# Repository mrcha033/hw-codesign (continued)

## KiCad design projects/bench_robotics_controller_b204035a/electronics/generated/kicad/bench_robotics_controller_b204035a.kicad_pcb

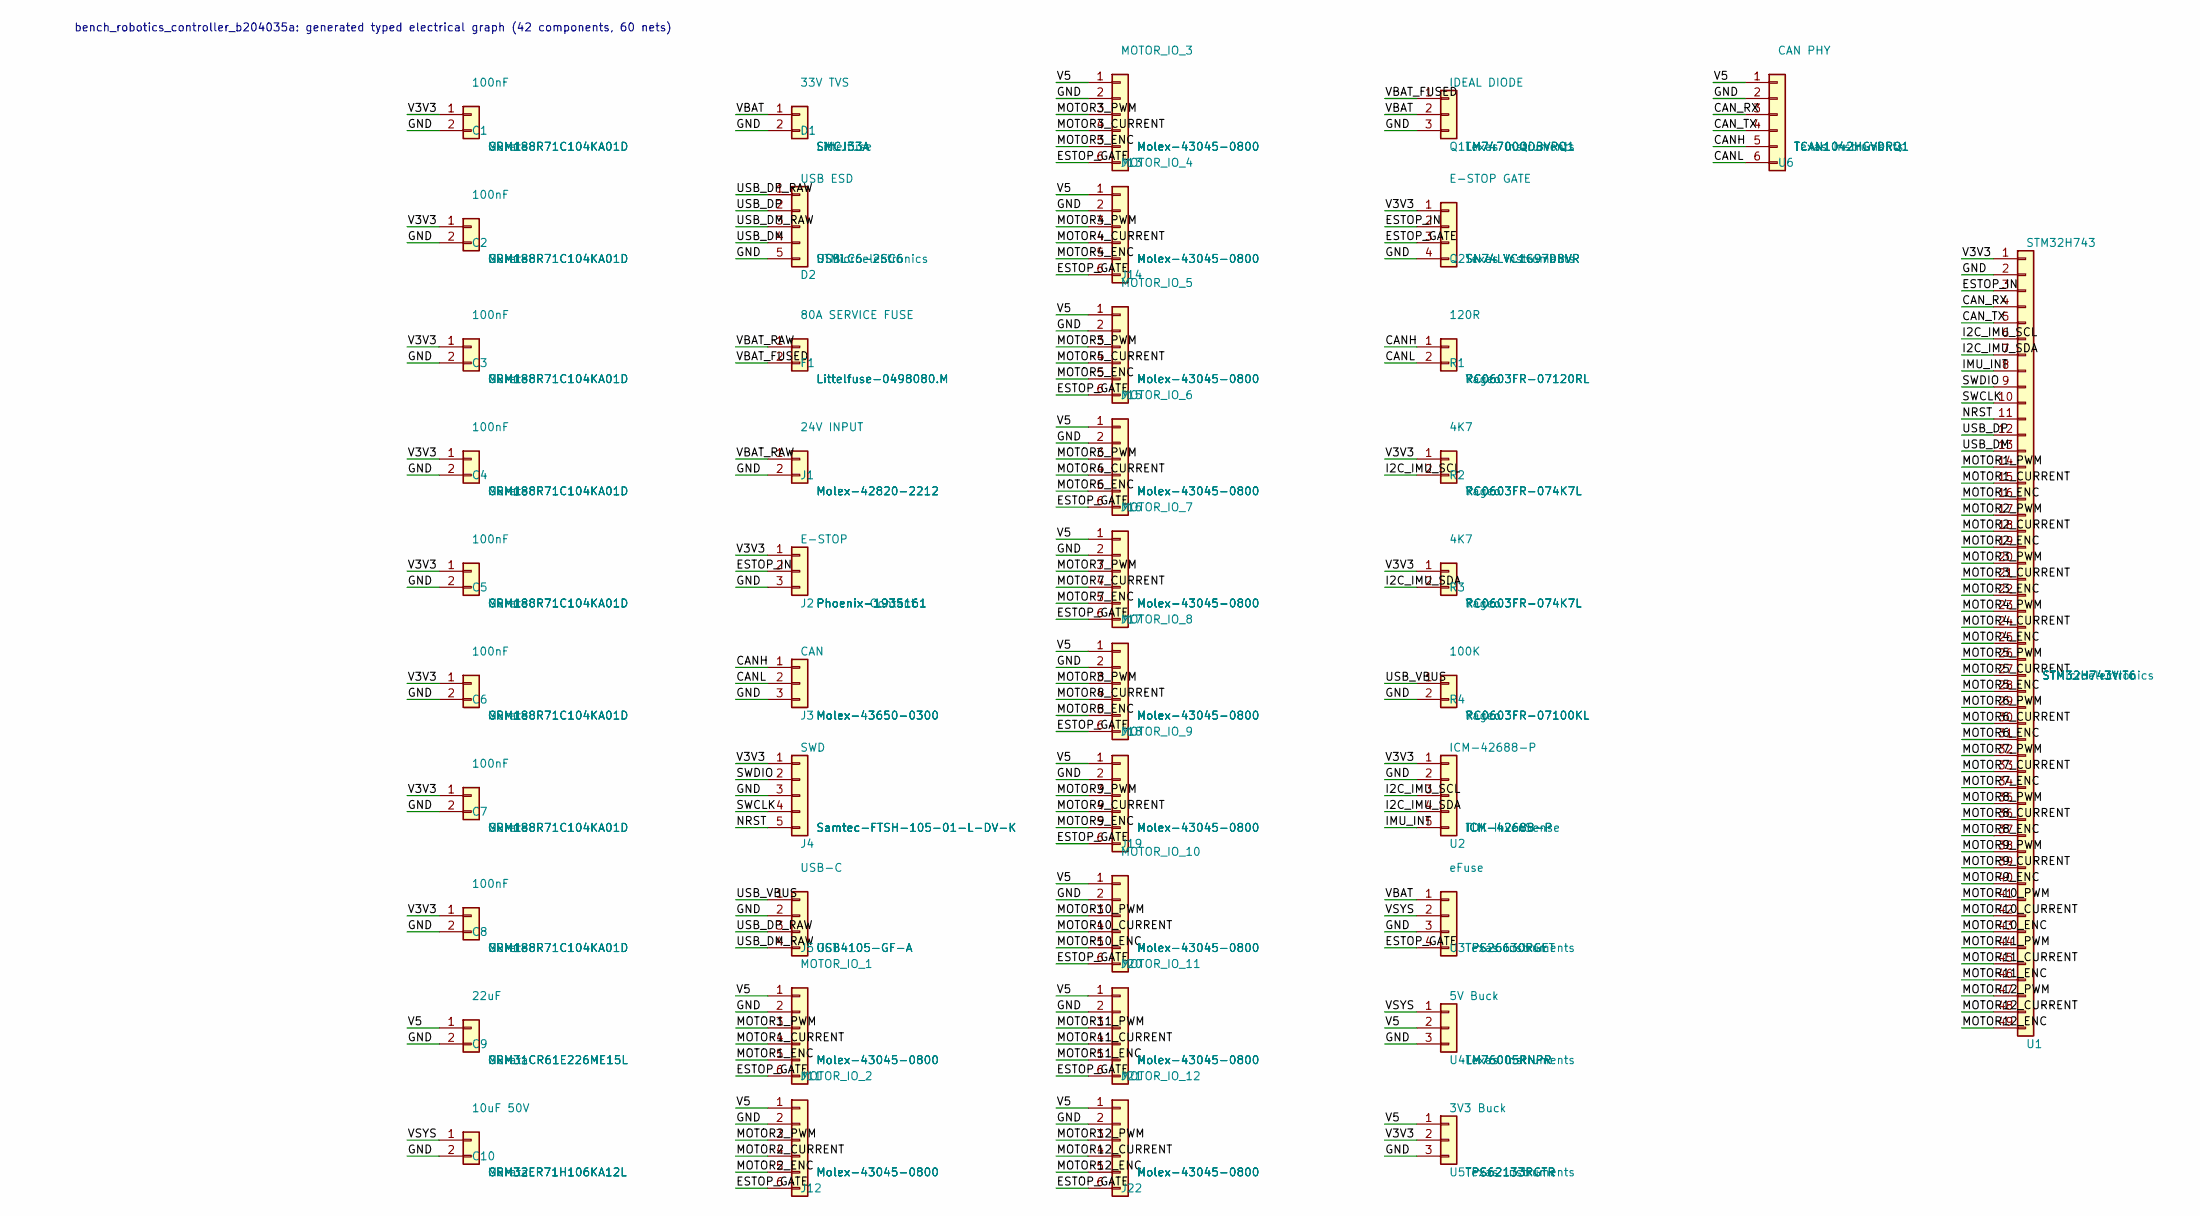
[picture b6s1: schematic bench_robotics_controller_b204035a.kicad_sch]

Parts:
C1, C2, C3, C4, C5, C6, C7, C8: 100nF; C_0603_1608Metric; MPN GRM188R71C104KA01D
C9: 22uF; C_1206_3216Metric; MPN GRM31CR61E226ME15L
C10: 10uF 50V; C_1210_3225Metric; MPN GRM32ER71H106KA12L
D1: 33V TVS; D_SMC; MPN SMCJ33A
D2: USB ESD; SOT-23-6; MPN USBLC6-2SC6
F1: 80A SERVICE FUSE; MIDI_Fuse; MPN Littelfuse-0498080.M
J1: 24V INPUT; MicroFit_2Pin; MPN Molex-42820-2212
J2: E-STOP; Phoenix_3Pin; MPN Phoenix-1935161
J3: CAN; MicroFit_3Pin; MPN Molex-43650-0300
J4: SWD; FTSH-105; MPN Samtec-FTSH-105-01-L-DV-K
J5: USB-C; USB_C_GCT_USB4105; MPN USB4105-GF-A
J11: MOTOR_IO_1; MicroFit_8Pin; MPN Molex-43045-0800
J12: MOTOR_IO_2; MicroFit_8Pin; MPN Molex-43045-0800
J13: MOTOR_IO_3; MicroFit_8Pin; MPN Molex-43045-0800
J14: MOTOR_IO_4; MicroFit_8Pin; MPN Molex-43045-0800
J15: MOTOR_IO_5; MicroFit_8Pin; MPN Molex-43045-0800
J16: MOTOR_IO_6; MicroFit_8Pin; MPN Molex-43045-0800
J17: MOTOR_IO_7; MicroFit_8Pin; MPN Molex-43045-0800
J18: MOTOR_IO_8; MicroFit_8Pin; MPN Molex-43045-0800
J19: MOTOR_IO_9; MicroFit_8Pin; MPN Molex-43045-0800
J20: MOTOR_IO_10; MicroFit_8Pin; MPN Molex-43045-0800
J21: MOTOR_IO_11; MicroFit_8Pin; MPN Molex-43045-0800
J22: MOTOR_IO_12; MicroFit_8Pin; MPN Molex-43045-0800
Q1: IDEAL DIODE; SOT-23-6; MPN LM74700QDBVRQ1
Q2: E-STOP GATE; SOT-23-6; MPN SN74LVC1G97DBVR
R1: 120R; R_0603_1608Metric; MPN RC0603FR-07120RL
R2, R3: 4K7; R_0603_1608Metric; MPN RC0603FR-074K7L
R4: 100K; R_0603_1608Metric; MPN RC0603FR-07100KL
U1: STM32H743; LQFP-100_14x14mm_P0.5mm; MPN STM32H743VIT6
U2: ICM-42688-P; LGA-14; MPN ICM-42688-P
U3: eFuse; VQFN-24-1EP; MPN TPS26630RGET
U4: 5V Buck; WQFN-30; MPN LM76005RNPR
U5: 3V3 Buck; VQFN-16; MPN TPS62133RGTR
U6: CAN PHY; SOIC-8_3.9x4.9mm_P1.27mm; MPN TCAN1042HGVDRQ1

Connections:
CANH: J3.1, R1.1, U6.5
CANL: J3.2, R1.2, U6.6
CAN_RX: U1.4, U6.3
CAN_TX: U1.5, U6.4
ESTOP_GATE: J11.6, J12.6, J13.6, J14.6, J15.6, J16.6, J17.6, J18.6, J19.6, J20.6, J21.6, J22.6, Q2.3, U3.4
ESTOP_IN: J2.2, Q2.2, U1.3
GND: C1.2, C2.2, C3.2, C4.2, C5.2, C6.2, C7.2, C8.2, C9.2, C10.2, D1.2, D2.5, J1.2, J2.3, J3.3, J4.3, J5.2, J11.2, J12.2, J13.2, J14.2, J15.2, J16.2, J17.2, J18.2, J19.2, J20.2, J21.2, J22.2, Q1.3, Q2.4, R4.2, U1.2, U2.2, U3.3, U4.3, U5.3, U6.2
I2C_IMU_SCL: R2.2, U1.6, U2.3
I2C_IMU_SDA: R3.2, U1.7, U2.4
IMU_INT: U1.8, U2.5
MOTOR1_CURRENT: J11.4, U1.15
MOTOR1_ENC: J11.5, U1.16
MOTOR1_PWM: J11.3, U1.14
MOTOR2_CURRENT: J12.4, U1.18
MOTOR2_ENC: J12.5, U1.19
MOTOR2_PWM: J12.3, U1.17
MOTOR3_CURRENT: J13.4, U1.21
MOTOR3_ENC: J13.5, U1.22
MOTOR3_PWM: J13.3, U1.20
MOTOR4_CURRENT: J14.4, U1.24
MOTOR4_ENC: J14.5, U1.25
MOTOR4_PWM: J14.3, U1.23
MOTOR5_CURRENT: J15.4, U1.27
MOTOR5_ENC: J15.5, U1.28
MOTOR5_PWM: J15.3, U1.26
MOTOR6_CURRENT: J16.4, U1.30
MOTOR6_ENC: J16.5, U1.31
MOTOR6_PWM: J16.3, U1.29
MOTOR7_CURRENT: J17.4, U1.33
MOTOR7_ENC: J17.5, U1.34
MOTOR7_PWM: J17.3, U1.32
MOTOR8_CURRENT: J18.4, U1.36
MOTOR8_ENC: J18.5, U1.37
MOTOR8_PWM: J18.3, U1.35
MOTOR9_CURRENT: J19.4, U1.39
MOTOR9_ENC: J19.5, U1.40
MOTOR9_PWM: J19.3, U1.38
MOTOR10_CURRENT: J20.4, U1.42
MOTOR10_ENC: J20.5, U1.43
MOTOR10_PWM: J20.3, U1.41
MOTOR11_CURRENT: J21.4, U1.45
MOTOR11_ENC: J21.5, U1.46
MOTOR11_PWM: J21.3, U1.44
MOTOR12_CURRENT: J22.4, U1.48
MOTOR12_ENC: J22.5, U1.49
MOTOR12_PWM: J22.3, U1.47
NRST: J4.5, U1.11
SWCLK: J4.4, U1.10
SWDIO: J4.2, U1.9
USB_DM: D2.4, U1.13
USB_DM_RAW: D2.3, J5.4
USB_DP: D2.2, U1.12
USB_DP_RAW: D2.1, J5.3
USB_VBUS: J5.1, R4.1
V3V3: C1.1, C2.1, C3.1, C4.1, C5.1, C6.1, C7.1, C8.1, J2.1, J4.1, Q2.1, R2.1, R3.1, U1.1, U2.1, U5.2
V5: C9.1, J11.1, J12.1, J13.1, J14.1, J15.1, J16.1, J17.1, J18.1, J19.1, J20.1, J21.1, J22.1, U4.2, U5.1, U6.1
VBAT: D1.1, Q1.2, U3.1
VBAT_FUSED: F1.2, Q1.1
VBAT_RAW: F1.1, J1.1
VSYS: C10.1, U3.2, U4.1

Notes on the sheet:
bench_robotics_controller_b204035a: generated typed electrical graph (42 components, 60 nets)

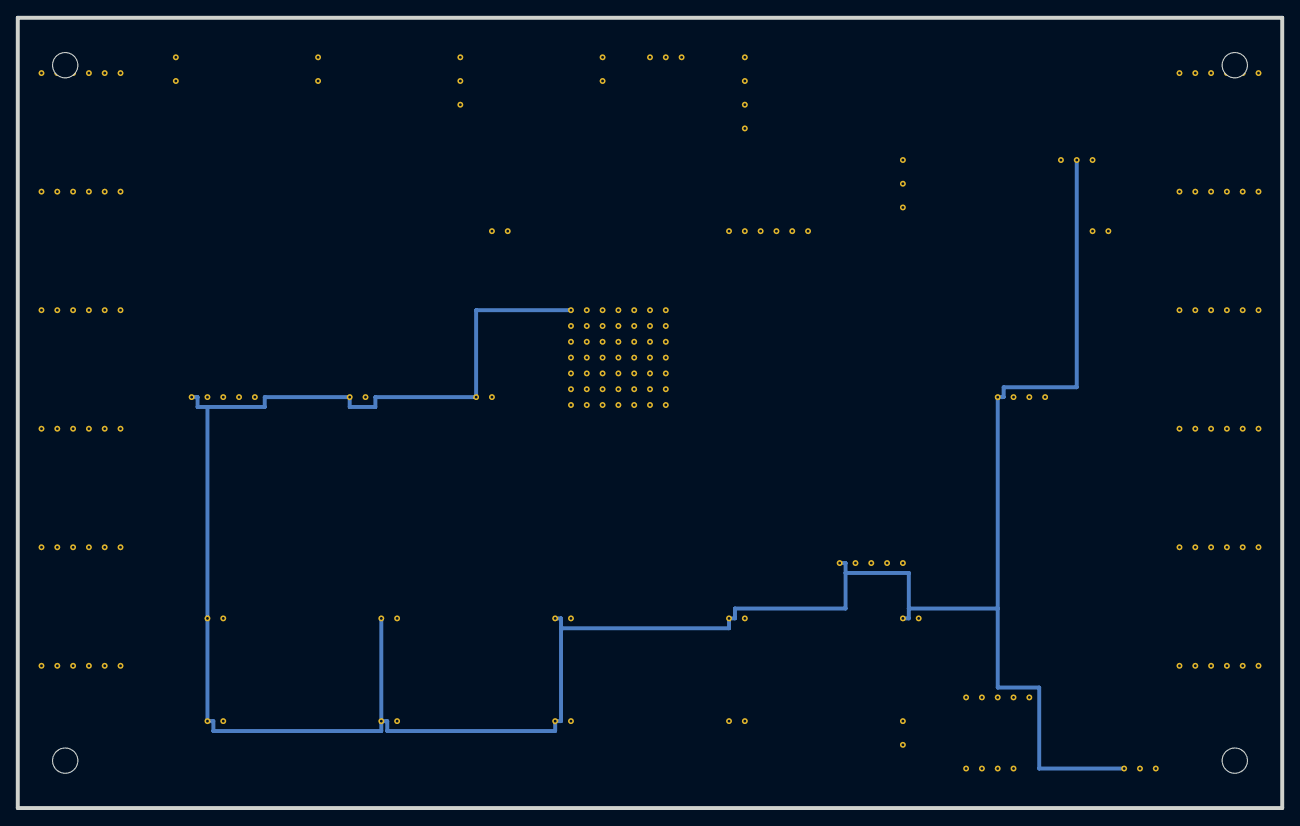
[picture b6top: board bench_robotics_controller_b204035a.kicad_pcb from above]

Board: 4 copper layers, 160.0 x 100.0 mm, 46 parts (0 on the bottom side), 60 nets.

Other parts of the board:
H1, H2, H3, H4: MountingHole; MountingHole_3.2mm_Pad

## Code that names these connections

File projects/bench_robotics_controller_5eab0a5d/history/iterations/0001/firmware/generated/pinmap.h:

#pragma once

#define PIN_ESTOP_IN "ESTOP_IN"
#define PIN_CAN_RX "CAN_RX"
#define PIN_CAN_TX "CAN_TX"
#define PIN_I2C_IMU_SCL "I2C_IMU_SCL"
#define PIN_I2C_IMU_SDA "I2C_IMU_SDA"
#define PIN_IMU_INT "IMU_INT"
#define PIN_USB_DP "USB_DP"
#define PIN_USB_DM "USB_DM"
#define PIN_MOTOR1_PWM "MOTOR1_PWM"
#define PIN_MOTOR1_CURRENT "MOTOR1_CURRENT"
#define PIN_MOTOR1_ENC "MOTOR1_ENC"
#define PIN_MOTOR2_PWM "MOTOR2_PWM"
#define PIN_MOTOR2_CURRENT "MOTOR2_CURRENT"
#define PIN_MOTOR2_ENC "MOTOR2_ENC"
#define PIN_MOTOR3_PWM "MOTOR3_PWM"
#define PIN_MOTOR3_CURRENT "MOTOR3_CURRENT"
#define PIN_MOTOR3_ENC "MOTOR3_ENC"
#define PIN_MOTOR4_PWM "MOTOR4_PWM"
#define PIN_MOTOR4_CURRENT "MOTOR4_CURRENT"
#define PIN_MOTOR4_ENC "MOTOR4_ENC"
#define PIN_MOTOR5_PWM "MOTOR5_PWM"
#define PIN_MOTOR5_CURRENT "MOTOR5_CURRENT"
#define PIN_MOTOR5_ENC "MOTOR5_ENC"
#define PIN_MOTOR6_PWM "MOTOR6_PWM"
#define PIN_MOTOR6_CURRENT "MOTOR6_CURRENT"
#define PIN_MOTOR6_ENC "MOTOR6_ENC"
#define PIN_MOTOR7_PWM "MOTOR7_PWM"
#define PIN_MOTOR7_CURRENT "MOTOR7_CURRENT"
#define PIN_MOTOR7_ENC "MOTOR7_ENC"
#define PIN_MOTOR8_PWM "MOTOR8_PWM"
#define PIN_MOTOR8_CURRENT "MOTOR8_CURRENT"
#define PIN_MOTOR8_ENC "MOTOR8_ENC"
#define PIN_MOTOR9_PWM "MOTOR9_PWM"
#define PIN_MOTOR9_CURRENT "MOTOR9_CURRENT"
#define PIN_MOTOR9_ENC "MOTOR9_ENC"
#define PIN_MOTOR10_PWM "MOTOR10_PWM"
#define PIN_MOTOR10_CURRENT "MOTOR10_CURRENT"
#define PIN_MOTOR10_ENC "MOTOR10_ENC"
#define PIN_MOTOR11_PWM "MOTOR11_PWM"
#define PIN_MOTOR11_CURRENT "MOTOR11_CURRENT"
#define PIN_MOTOR11_ENC "MOTOR11_ENC"
#define PIN_MOTOR12_PWM "MOTOR12_PWM"
#define PIN_MOTOR12_CURRENT "MOTOR12_CURRENT"
#define PIN_MOTOR12_ENC "MOTOR12_ENC"

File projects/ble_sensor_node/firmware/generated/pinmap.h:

#pragma once

#define PIN_I2C_SCL "P0.02"
#define PIN_I2C_SDA "P0.03"
#define PIN_CHG_STAT "P0.04"
#define PIN_TEMP_INT "P0.05"
#define PIN_FUEL_ALRT "P0.06"
#define PIN_LED_BLE "P0.08"
#define PIN_UART_TX "P0.28"
#define PIN_UART_RX "P0.29"
#define PIN_SWDCLK "SWDCLK"
#define PIN_SWO "SWO"
#define PIN_USB_DM "D-"
#define PIN_USB_DP "D+"

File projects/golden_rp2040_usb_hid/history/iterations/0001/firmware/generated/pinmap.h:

#pragma once

#define PIN_XIN "XIN"
#define PIN_XOUT "XOUT"
#define PIN_MCU_RUN "RUN"
#define PIN_USB_DM "USB_DM"
#define PIN_USB_DP "USB_DP"
#define PIN_QSPI_D3 "QSPI_SD3"
#define PIN_QSPI_CLK "QSPI_SCLK"
#define PIN_QSPI_MOSI "QSPI_SD0"
#define PIN_QSPI_D2 "QSPI_SD2"
#define PIN_QSPI_MISO "QSPI_SD1"
#define PIN_QSPI_CS "QSPI_CSn"

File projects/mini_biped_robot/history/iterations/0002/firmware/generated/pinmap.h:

#pragma once

#define PIN_XIN32 "PA00_XIN32"
#define PIN_XOUT32 "PA01_XOUT32"
#define PIN_IMU_INT1 "PA18_SERCOM3_2"
#define PIN_I2C_SDA "PA22_SDA"
#define PIN_I2C_SCL "PA23_SCL"
#define PIN_USB_DM "PA24_USBDM"
#define PIN_USB_DP "PA25_USBDP"
#define PIN_MCU_NRST "~RESETN"
#define PIN_VDDCORE "VDDCORE"

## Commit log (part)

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2026-06-14 Initial commit: hw-codesign-platform v0.1.0
    Hardware co-design platform CLI, MCP server, schemas, tests, and
    example quadruped robot controller project including electronics,
    firmware, mechanical, and iteration history.
2026-06-14 feat: component resolver, provenance tracking, and tscircuit backend gate
    - Add ComponentResolver and artifact_provenance to wire real component
    data (MPN, footprint, lifecycle) into the electrical graph
    - Introduce TSCircuitBackend as the first release-eligible compiled
    electronics backend; reference backend now explicitly blocks release
    - Move electronics design intent from .ato source files to annotated
    .intent.md files under electronics/intent/
2026-06-14 fix: update prepare_release logic to block on unresolved critical assumptions and adjust footprint parity checks
2026-06-15 feat: constraint-driven placement proposal layer (roadmap #5)
    Add structured, provenance-tagged component placement with a checkable
    constraint model, scoped as a placement proposal rather than autonomous
    layout.
    - placement.py: Placement/PlacementConstraint/PlacementProposal dataclasses;
    propose_placement derives board/mounting-hole keepouts, connector-edge
    (reusing max_connector_edge_distance_mm), decoupling-proximity (represented
2026-06-15 feat: add hw export-review command producing normalized review bundle (steps 2-3)
    service.export_review() aggregates persisted gate reports, placement
    proposal metadata, component resolution summary, requirements lowering
    summary, and assumption state into a single bundle.json. The canonical
    content (excluding generated_at) is SHA-256 hashed into bundle_hash so
    consecutive exports are byte-identical deterministically.
    cli.py wires the export-review subcommand and also stubs upload_review()
2026-06-15 test: add review bundle test suite (5 tests)
    Covers: schema validation of produced bundle, hash determinism across
    consecutive exports, HTML generation, graceful no-prior-checks path,
    and upload_review blocked-without-destination guard.
2026-06-15 feat: add hw_codesign.contracts public package with full tool registry and schemas
    Introduces `hw_codesign.contracts` as the single source of truth for the
    local-and-cloud MCP contract surface:
    - TOOL_REGISTRY: 36 ToolDef entries each carrying name, description,
    input_schema, output_schema, and execution_mode
    - 12 shared output schemas in _schemas.py (gate_report, gate_report_collection,
    electronics_source_result, repair_plan, iteration_result, etc.) referenced
2026-06-15 fix setup-uv action version
2026-06-15 fix: verify ESP32-S3 library, add Windows CI, strengthen atopile tests
    Component verification:
    - esp32s3_wroom_1: updated to verified: true, review_status: approved after
    checking against KiCad RF_Module library installed at
    /Applications/KiCad/KiCad.app/Contents/SharedSupport; corrected package
    from LCC-52 to LCC-41 (41 castellated pads + thermal), library_id from
    HW_Curated placeholder to RF_Module:ESP32-S3-WROOM-1, pin numbers and
2026-06-16 feat: sensor_data_logger second board family — 2-layer, ESP32-S3, USB-C
    Adds a complete second board template (sensor_data_logger) fully parallel
    to robotics_controller_full, with all generation paths dispatching on
    architecture:
    - electronics_design: build_sensor_data_logger_graph() for ESP32-S3-WROOM-1,
    USB-C/ESD/buck power tree, ICM-42688-P IMU, I2C pull-ups, UART debug header
    - board_layout: sensor_data_logger anchor table + _seed_table_for_graph() dispatch
2026-06-16 fix: Windows CI — bundle KiCAD symbols and fix tsx binary on win32
    74 tests were failing because kicad-symbols is only installed on the
    Linux CI runner (via apt). The Windows runner has no KiCAD, so
    kicad_sch_api throws LibraryError on every schematic generation call.
    Fix: bundle a minimal Connector_Generic.kicad_sym (Conn_01x01–50) in
    parts/kicad_symbols/ and add a session-scoped autouse fixture in
    conftest.py that sets KICAD_SYMBOL_DIR to the bundled path when no
2026-06-16 fix: use bundled KiCAD symbols on all platforms, pins inside unit sub-symbol
    Two issues remained after the previous fix:
    1. kicad_sch_api._extract_pins_from_symbol only finds pins inside the unit
    sub-symbol (e.g. Conn_01x02_1_1), but the generated file had pins at the
    parent symbol level. Locally list_pins() still worked via the embedded
    schematic copy, but on Windows CI the pin lookup path disagreed, causing
    "Missing generated schematic pin C1.1" for all 76 tests.
2026-06-16 fix: pass relative posix path to tscircuit CLI, expose stderr on failure
    The tscircuit CLI uses the entry file path to construct its dist output
    directory name. When given an absolute Windows path (D:\a\hw-cli\...),
    it creates dist/D:\a\hw-cli\... which contains a colon — invalid on
    Windows filesystems — causing a non-zero exit code.
    Fix: compute the entry path relative to platform_root (the cwd for the
    subprocess) and pass it as a POSIX-format string, e.g.
2026-06-16 fix: MCP protocol correctness — envelope gaps, python_netlist gate, stale detection
    - check_release_gate: accept python_netlist as release-eligible backend (was
    incorrectly blocked via backend_release_policy); use backend-specific required
    artifact list (compiled_netlist.json instead of gerbers/drill) and filter out
    intentionally-BLOCKED layout/manufacturing gates that python_netlist never emits
    - _enrich: replace setdefault with direct dict merge ({**result, **extra}) so
    safety-critical envelope fields (release_eligible, candidate_only,
2026-06-16 docs: fix envelope accuracy, add missing tools, badges, and visual polish
    Accuracy fixes:
    - Canonical workflow: hw_check_release_gate sets release_eligible=true on pass;
    hw_export_release_bundle sets it on released — remove misleading "only this tool"
    - Envelope table: release_eligible=false on ALL tools (not just generation/requirements)
    - Gate semantics footer matches updated table
    New content:
2026-06-17 feat: Phase A — agent-authored mechanical part design
    Introduces the first authoring domain: agents can now proactively design
    3D-printable mechanical parts by expressing design intent, not by filling
    in enclosure dimensions.
    New part library (backends/parts/):
    - PcbMountBracket: L/U bracket for 2020/4040 extrusion or panel mounting
    - StandoffTower: M2–M4 standoff with threaded bore and optional flange
2026-06-17 feat: Phase 6 — standalone export, dashboard, hosted upload, review comments
    Implements all four GUI/cloud/collaboration capabilities:
    - Standalone HTML export: build_standalone_html() embeds bundle JSON as
    window.__BUNDLE_DATA; _VIEWER_HTML updated to use it (gated polling,
    gated add-comment link). service.export_standalone_review() + CLI
    export-standalone-review + hw_share_review MCP tool.
    - Multi-project dashboard: workspace.list_projects() scans projects dir;
2026-06-21 parts: add component alternatives, single-source justifications, and resistor entries to all role sets
    All three role sets now carry `alternatives` (footprint-compatible substitute components with
    required review flags) and `single_source_justifications` (per-role sole-source rationale and
    mitigation path) so the sourcing-resilience gate has evidence to evaluate. Two new resistor SKUs
    (rc0603_1k, rc0603_10k) added to the curated supplier catalog as drop-in resistor alternatives.
    robotics_controller component pin list extended to the full 100-pad LQFP footprint.
2026-06-21 feat: MCP server and contracts — design_candidate, design-space, physical qualification, and grounding tools
    Five new MCP tools registered: hw_design_candidate, hw_explore_design_space,
    hw_run_grounding_benchmark, hw_generate_physical_qualification_plan, hw_record_physical_evidence.
    hw_run_design_iteration goal string updated to match the service change. atopile backend noted in
    the reference-backend release-blocking message. JSON schema for design_candidate_result added to
    SHARED_SCHEMAS including all required properties (semantic_representation, sourcing_choices,
    dependency_graph, grounding_summary). component_resolution type corrected from object to array in
2026-06-21 docs: restructure as wiki — short README landing page + six focused docs/ files
    README trimmed from 636 to 150 lines: pitch, install, quickstart, doc table, dev setup,
    known limits, generated example. Technical depth moved to docs/:
    docs/architecture.md — board families, backend maturity, repo layout, module map (new)
    docs/capabilities.md — full capabilities reference: electronics, placement, mechanical,
    firmware, sourcing, design-space, release (new)
    docs/mcp-tools.md — agent workflow, response envelope, all tools, MCP resources,
2026-06-21 fix: use as_posix() for path strings in semantic representation and reviewable_artifacts
    str(Path(...)) produces backslash separators on Windows, breaking test
    assertions that use .endswith("/..."). Switch to Path.as_posix() so all
    returned path strings use forward slashes on every platform.
    Fixes test_p1_p3_platform.py::test_design_candidate_is_cross_domain_primary_workflow
    on Windows CI (pre-existing failure, now resolved).
2026-06-21 feat: add ble_sensor_node and sensor_data_logger generated project workspaces
    Runs design-candidate end-to-end for both board families, producing
    candidate bundles, validation reports, portable review bundles, electronics
    graph, semantic schematic, BOM, firmware pinmap, and mechanical contract.
    Gate summary without native toolchain:
    - ble_sensor_node: 24 pass / 3 fail / 14 blocked (41 gates)
    - sensor_data_logger: 26 pass / 1 fail / 14 blocked (41 gates)
2026-06-21 feat: H0 benchmark harness — one-line spec → design_until_release pass-rate
    Add the H0 milestone: a reproducible benchmark that measures how often the
    agent takes a one-line hardware spec all the way through design_until_release.
    - `_EXTERNAL_GATES` / `_STRUCTURAL_BLOCKED_GATES` constants partition gates
    into software-only vs native-toolchain so CI can track regression without
    KiCad/Zephyr installed.
    - `design_until_release()` now returns `"software_gates_ready"` when all
2026-06-28 fix: BLE sensor node autorouting — 0 unrouted, gate infrastructure
    Routing fixes:
    - board_layout.py: Rearrange _BLE_SENSOR_NODE_ANCHORS so pads don't collide.
    U3 → (40,6) moves U3-4 GND from y=27 to y=15, clearing the signal channel.
    C2 → (26,19) moves C2-2 GND from (33,19) away from U1-5 I2C_SCL.
    - electronics_design.py: Reorder J2 pins (GND at pin-1, signals in U1 x-order
    for zero route crossings). Swap USB_DP/USB_DM to correct pin order on U1.
2026-06-29 fix: rp2040 firmware crash + robotics CAN termination placement
    - generators.py: skip firmware modules with unknown/None behavior
    (driver/library stubs have no behavior key; render_module raised
    ValueError and aborted rp2040_usb_hid firmware generation)
    - board_layout.py: move R1 (CAN termination) from (136,27) to (104,20)
    so CANH/CANL routing distance from U6 drops ~46mm → ~9mm
2026-06-29 fix: return BLOCKED (not FAIL) when Zephyr board not in installed SDK
    When cmake fails quickly with "No board named" or "Board qualifiers not found",
    the board is simply absent from the installed Zephyr SDK — not a design error.
    Return BLOCKED so the H0 denominator excludes the gate (same as toolchain absent).
2026-06-29 fix: make generate_physical_qualification_plan non-fatal in run_all_checks
    The function occasionally fails with ProjectNotFoundError during the second
    design iteration (repair loop). Wrapping it in try/except prevents the crash
    from aborting the benchmark — the physical_qualification_report reads the plan
    file if present, and silently skips it if missing.
2026-06-30 chore: add benchmark evidence artifacts
2026-06-30 feat: expose backend release tier partitions
2026-06-30 fix: complete rp2040 package pin contract
2026-06-30 fix: align rp2040 clearance profile
2026-06-30 chore: add 5eab0a5d benchmark snapshot
2026-06-30 fix: enforce python netlist release tier boundary
2026-06-30 feat: expose canonical fabrication backend contract
